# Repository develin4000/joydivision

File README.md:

# joydivision
Source for the digital joystick adapter JoyDivision - http://www.onyxsoft.se/joydivision.html

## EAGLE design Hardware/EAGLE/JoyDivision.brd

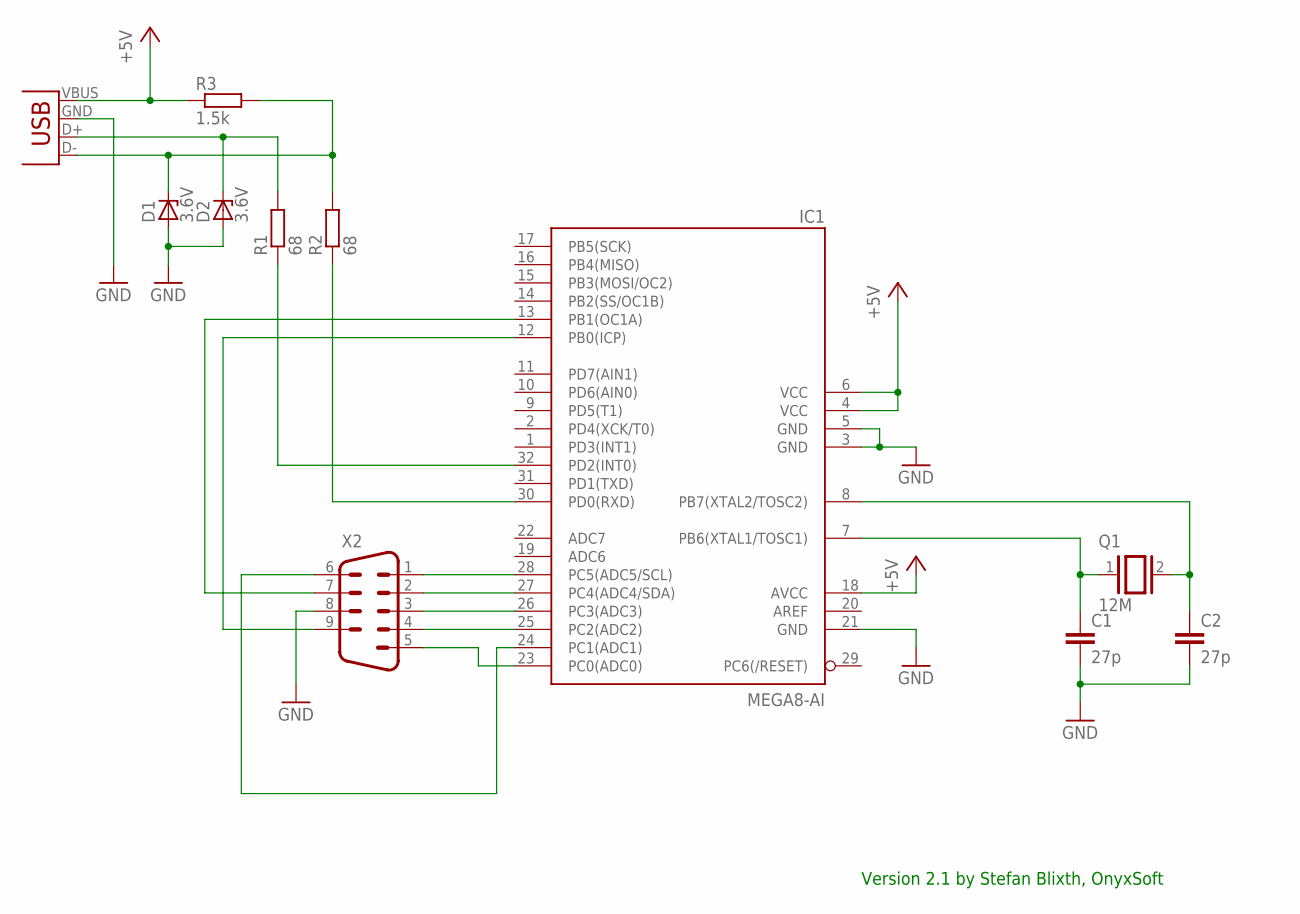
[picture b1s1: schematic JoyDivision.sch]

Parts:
C1, C2: 27p; C0805
D1, D2: 3.6V; SOD80C
IC1: MEGA8-AI; TQFP32-08
JP1: USB-A-H
Q1: 12M; QS
R1, R2: 68; M0805
R3: 1.5k; M0805
X2: M09D

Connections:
+5V: IC1.4 (VCC), IC1.6 (VCC), IC1.18 (AVCC), JP1.VBUS (GND), R3.1
GND: C1.2, C2.2, D1.A, D2.A, IC1.3 (GND), IC1.5 (GND), IC1.21 (GND), JP1.GND (VBUS), X2.8
unnamed: D1.C, JP1.D- (D+), R2.2, R3.2
unnamed: D2.C, JP1.D+ (D-), R1.2
unnamed: IC1.30 (PD0(RXD)), R2.1
unnamed: IC1.32 (PD2(INT0)), R1.1
unnamed: C1.1, IC1.7 (PB6(XTAL1/TOSC1)), Q1.1
unnamed: C2.1, IC1.8 (PB7(XTAL2/TOSC2)), Q1.2
unnamed: IC1.28 (PC5(ADC5/SCL)), X2.1
unnamed: IC1.27 (PC4(ADC4/SDA)), X2.2
unnamed: IC1.26 (PC3(ADC3)), X2.3
unnamed: IC1.25 (PC2(ADC2)), X2.4
unnamed: IC1.24 (PC1(ADC1)), X2.6
unnamed: IC1.23 (PC0(ADC0)), X2.5
unnamed: IC1.12 (PB0(ICP)), X2.9
unnamed: IC1.13 (PB1(OC1A)), X2.7

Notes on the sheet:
Version 2.1 by Stefan Blixth, OnyxSoft

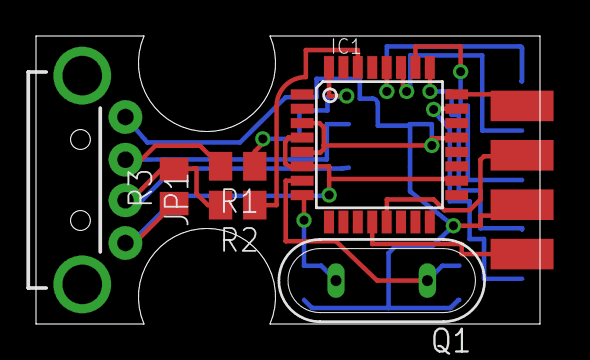
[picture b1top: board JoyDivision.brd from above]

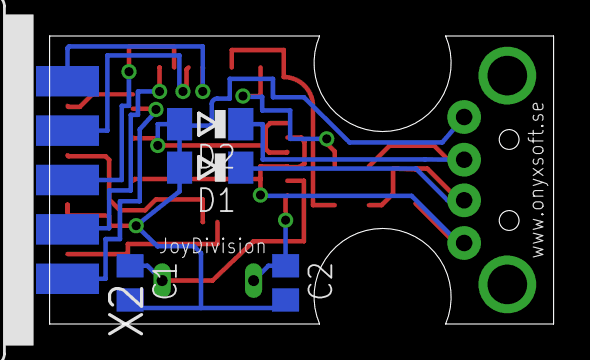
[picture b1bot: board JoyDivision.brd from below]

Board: 2 copper layers, 28.0 x 16.0 mm, 11 parts (5 on the bottom side), 16 nets.

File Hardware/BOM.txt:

Orginal JoyDivision :

Qty Value    Device            Package   Parts   Description
1            M09D              M09D      X2      SUB-D
1   1.5k     R-EU_M0805        M0805     R3      RESISTOR, European symbol
1   12M      XTAL/S            QS        Q1      CRYSTAL
2   27p      C-EUC0805         C0805     C1, C2  CAPACITOR, European symbol
2   3.6V     ZENER-DIODESOD80C SOD80C    D1, D2  Z-Diode
2   68       R-EU_M0805        M0805     R1, R2  RESISTOR, European symbol
1   MEGA8-AI MEGA8-AI          TQFP32-08 IC1     MICROCONTROLLER AVR ATMEGA8-8AU
1   USB-A-H  USB-A-H           USB-A-H   JP1     USB Connectors


Dual JoyDivision :

Qty Value    Device            Package   Parts   Description
1            DB25D             M25D      X1      Various DB25 connectors                                        
1            M04PTH            1X04      *       Solder Pads                                                       
1   1.5k     R-EU_M0805        M0805     R3      RESISTOR, European symbol                                      
1   12M      XTAL/S            QS        Q1      CRYSTAL                                                        
2   27p      C-EUC0805         C0805     C1, C2  CAPACITOR, European symbol                                     
2   3.6V     ZENER-DIODESOD80C SOD80C    D1, D2  Z-Diode                                                        
2   68       R-EU_M0805        M0805     R1, R2  RESISTOR, European symbol                                      
1   MEGA8-AI MEGA8-AI          TQFP32-08 IC1     MICROCONTROLLER

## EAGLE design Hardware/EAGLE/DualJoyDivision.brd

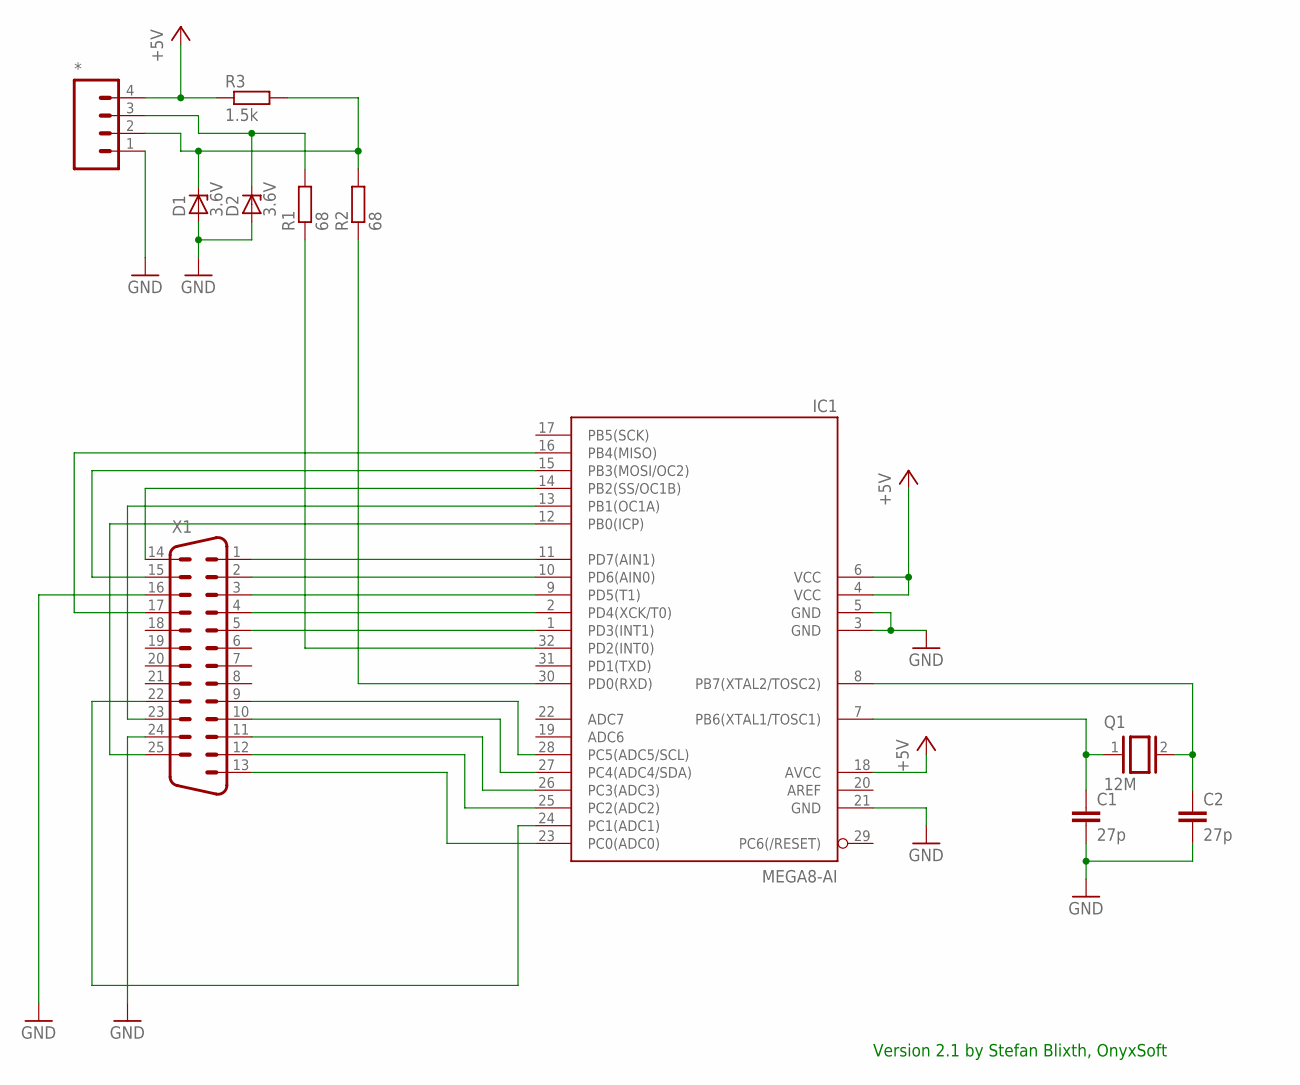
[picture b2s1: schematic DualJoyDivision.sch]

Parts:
*: M04PTH; 1X04
C1, C2: 27p; C0805
D1, D2: 3.6V; SOD80C
IC1: MEGA8-AI; TQFP32-08
Q1: 12M; QS
R1, R2: 68; M0805
R3: 1.5k; M0805
X1: DB25D; M25D

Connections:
+5V: *.4, IC1.4 (VCC), IC1.6 (VCC), IC1.18 (AVCC), R3.1
GND: *.1, C1.2, C2.2, D1.A, D2.A, IC1.3 (GND), IC1.5 (GND), IC1.21 (GND), X1.16, X1.24
unnamed: *.2, D1.C, R2.2, R3.2
unnamed: *.3, D2.C, R1.2
unnamed: IC1.30 (PD0(RXD)), R2.1
unnamed: IC1.32 (PD2(INT0)), R1.1
unnamed: C1.1, IC1.7 (PB6(XTAL1/TOSC1)), Q1.1
unnamed: C2.1, IC1.8 (PB7(XTAL2/TOSC2)), Q1.2
unnamed: IC1.28 (PC5(ADC5/SCL)), X1.9
unnamed: IC1.27 (PC4(ADC4/SDA)), X1.10
unnamed: IC1.26 (PC3(ADC3)), X1.11
unnamed: IC1.25 (PC2(ADC2)), X1.12
unnamed: IC1.24 (PC1(ADC1)), X1.22
unnamed: IC1.23 (PC0(ADC0)), X1.13
unnamed: IC1.12 (PB0(ICP)), X1.25
unnamed: IC1.13 (PB1(OC1A)), X1.23
unnamed: IC1.11 (PD7(AIN1)), X1.1
unnamed: IC1.10 (PD6(AIN0)), X1.2
unnamed: IC1.9 (PD5(T1)), X1.3
unnamed: IC1.2 (PD4(XCK/T0)), X1.4
unnamed: IC1.1 (PD3(INT1)), X1.5
unnamed: IC1.14 (PB2(SS/OC1B)), X1.14
unnamed: IC1.15 (PB3(MOSI/OC2)), X1.15
unnamed: IC1.16 (PB4(MISO)), X1.17

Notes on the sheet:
Version 2.1 by Stefan Blixth, OnyxSoft

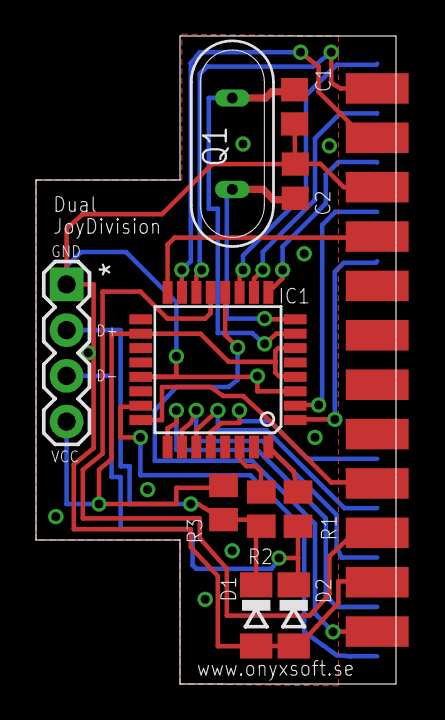
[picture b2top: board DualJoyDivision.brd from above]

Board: 2 copper layers, 20.0 x 36.0 mm, 11 parts (1 on the bottom side), 24 nets.

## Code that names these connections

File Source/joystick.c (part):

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
      // Read the status of the axis...
      if (tmp & (1<<PD1)) {axis_x = (thec64 || thea500) ? 0xff : 0x7f;} // Right
      if (tmp & (1<<PD3)) {axis_x = (thec64 || thea500) ? 0x00 : 0x81;} // Left
      if (tmp & (1<<PD0)) {axis_y = (thec64 || thea500) ? 0x00 : 0x81;} // Up

      // Read the status of the buttons...
      if (tmp & (1<<PD4)) {b1 = 1;} // Button 1
      if (tmp & (1<<PD5)) {b2 = 1;} // Button 2

      currState = PINB;
      tmp = currState^0xff;

      if (tmp & (1<<PB2)) {axis_y = (thec64 || thea500) ? 0xff : 0x7f;} // Down

#else
      currState = PINC;
      tmp = currState^0xff;

      // Read the status of the axis...
      if (tmp & (1<<PC2)) {axis_x = (thec64 || thea500) ? 0xff : 0x7f;} // Right
      if (tmp & (1<<PC3)) {axis_x = (thec64 || thea500) ? 0x00 : 0x81;} // Left
      if (tmp & (1<<PC4)) {axis_y = (thec64 || thea500) ? 0xff : 0x7f;} // Down 
      if (tmp & (1<<PC5)) {axis_y = (thec64 || thea500) ? 0x00 : 0x81;} // Up 

      // Read the status of the buttons...
      if (tmp & (1<<PC1)) {b1 = 1;} // Button 1
      if (tmp & (1<<PC0)) {b3 = 1;} // Button 3

      currState = PINB;
      tmp = currState^0xff;

      if (tmp & (1<<PB0)) {b2 = 1;} // Button 2
#endif
   }
   else // joyport == JOYPORT2
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      tmp = currState^0xff;

      // Read the status of the axis...
      if (tmp & (1<<PD4)) {axis_x = (thec64 || thea500) ? 0xff : 0x7f;} // Right
      if (tmp & (1<<PD5)) {axis_x = (thec64 || thea500) ? 0x00 : 0x81;} // Left
      if (tmp & (1<<PD6)) {axis_y = (thec64 || thea500) ? 0xff : 0x7f;} // Down
      if (tmp & (1<<PD7)) {axis_y = (thec64 || thea500) ? 0x00 : 0x81;} // Up

      // Read the status of the buttons...
      if (tmp & (1<<PD3)) {b3 = 1;} // Button 3

      currState = PINB;
      tmp = currState^0xff;

      if (tmp & (1<<PB2)) {b1 = 1;} // Button 1
      if (tmp & (1<<PB4)) {b2 = 1;} // Button 2

   }
   activeBuffer.axis_x  = axis_x;
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            6  ¯¯¯¯¯¯¯¯¯ 9

   Pin   Joystick     AVR-Pin (Port 1)   AVR-Pin (Port 2)     Edu Arana Adapter
   1     Up           PC5                PD7                  PD0
   2     Down         PC4                PD6                  PB2
   3     Left         PC3                PD5                  PD3
   4     Right        PC2                PD4                  PD1
   5     n/c          PC0                PD3                  ---
   6     Button1      PC1                PB2                  PD4
   7     +5V          PB1                PB3                  ---
   8     GND          GND                GND                  GND
   9     Button2      PB0                PB4                  PD5  */

   // Init PortB
   DDRB  = 0x00;
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
/*
   // Enable following if you own a JoyFi wireless transmitter/reciever -> http://store.ribit.se/
   SETBIT(DDRB, PB1);  // Enable PB1 as an output
   SETBIT(PORTB, PB1); // Enable PB1 / VCC
   SETBIT(DDRB, PB3);  // Enable PB3 as an output
   SETBIT(PORTB, PB3); // Enable PB3 / VCC
*/
}

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
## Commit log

2017-12-17 Added msx, amstrad and combo NES-SNES firmware plus NES/SNES-adaptation cable information
2019-08-03 Added support for THEC64 mini console
2019-08-15 Adjusted the non-joystick sources to comply with the correct HID report size
2019-08-15 Adjusted the non-joystick sources ro comply with the correct HID report size
2019-12-24 Adjusted the report type so the firmware works with the latest THEC64 firmware
2020-01-16 Cleaned up the HID report for THEC64 handling, added support for the Edu Arana joystick adapter
2020-10-06 Updated joystick firmware to work with THEC64 1.3.2 firmware
2022-04-15 Updated joystick firmware to work with latest THEC64 and also the new A500 mini

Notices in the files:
Source/joystick.c:
->= JoyDivision - USB joystick adapter - (c) Copyright 2016-2022 OnyxSoft =<-
->= it under the terms of the GNU General Public License as published by =<-
parts and their libraries:
SparkFun-Connectors: Licensing: Creative Commons ShareAlike 4.0 International - https://creativecommons.org/licenses/by-sa/4.0
